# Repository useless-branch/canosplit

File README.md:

# canosplit
CAN splitter node add nodes to bus and insert power

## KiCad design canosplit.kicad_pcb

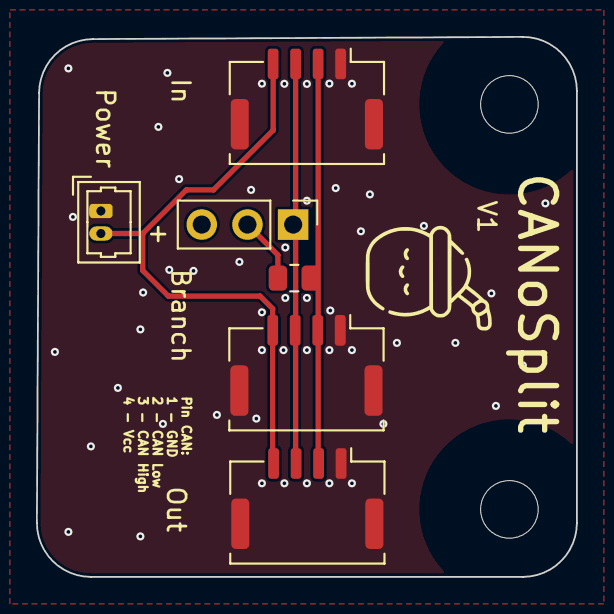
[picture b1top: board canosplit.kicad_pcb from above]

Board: 2 copper layers, 30.0 x 30.0 mm, 6 parts (0 on the bottom side), 5 nets.

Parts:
J1: In; Molex_CLIK-Mate_502382-0470_1x04-1MP_P1.25mm_Vertical
J2: Out; Molex_CLIK-Mate_502382-0470_1x04-1MP_P1.25mm_Vertical
J3: Branch; Molex_CLIK-Mate_502382-0470_1x04-1MP_P1.25mm_Vertical
J4: Power in; Molex_PicoBlade_53047-0210_1x02_P1.25mm_Vertical
JP1: Termination; PinHeader_1x03_P2.54mm_Vertical
R1: 120R; R_0805_2012Metric

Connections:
+36V: J1.4, J2.4, J3.4, J4.2
/CAN_H: J1.3, J2.3, J3.3, JP1.1 (A)
/CAN_L: J1.2, J2.2, J3.2, R1.2
GND: J1.1, J1.MP (MountPin), J2.1, J2.MP (MountPin), J3.1, J3.MP (MountPin), J4.1
unnamed: JP1.2 (B), R1.1

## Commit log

2021-11-15 researched parts
2021-11-16 updated after meeting
2021-11-17 updated board with new connector
2021-12-01 updated logo and text
2022-02-27 updated project
